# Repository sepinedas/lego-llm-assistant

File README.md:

# LEGO LLM Assistant

An intelligent voice-controlled LEGO robot powered by Large Language Models (LLMs) and speech recognition. This project combines hardware control with advanced AI to create an interactive robotic assistant.

## Overview

The LEGO LLM Assistant is a Go-based application that enables voice interaction with LEGO hardware through AI-powered natural language processing. The system captures audio input, processes it through speech-to-text, integrates with Google's Generative AI, and displays emotional reactions on expressive LED displays.

## Features

- **Voice Control**: Real-time audio capture and speech-to-text processing using Vosk
- **AI Integration**: Powered by Google's Generative AI API for intelligent responses
- **LEGO Hardware Control**: Display control via periph.io library
- **Expressive Displays**: Multiple animated face displays showing emotions and reactions
- **Wake Word Detection**: Custom wake word detection model
- **Audio Output**: Speaker audio playback for responses

## Architecture

### Core Components

- **`main.go`** - Main application entry point (not shown)
- **`audio.go`** - Audio capture and processing utilities
- **`display.go`** - Display rendering and text output system
- **`genai-client.go`** - Google Generative AI client integration
- **`lego-agent.go`** - LEGO main control logic
- **`wake-model.go`** - Wake word detection model handling
- **`periph.go`** - Hardware peripheral initialization

### Hardware Design

#### Final LEGO Robot Concept

The complete assembled robot features:
- **Head**: Display with microphone for voice input
- **Body**: Yellow and blue LEGO structure with mounting plate
- **Face Displays**: Three expressive circular LED displays showing emotions:
  - Two upper displays for eyes (showing sad/happy expressions)
  - One lower display for mouth (showing smile/neutral/sad emotions)

#### Custom Control PCB

The "Maya" control board is a custom-designed PCB that serves as the brain of the robot:

**Board Features:**
- Multiple I2C/SPI communication headers
- Named control headers for:
  - **Mouth1**: Lower face display control
  - **Left1/Right1**: Display control
  - **Head_y**: Head rotation control
- Central "Maya" processor area with trace routing
- Power distribution system (VDD/GND rails)
- Compact form factor with 4 mounting holes
- Gold-plated connector pads for durability
- Purple FR4 substrate for visibility and professional appearance

#### Electrical Schematic

The system includes comprehensive electrical design with:
- Display driver circuits for the three LED face displays
- Audio amplification stage for speaker output
- Power management and regulation
- Signal conditioning for sensor inputs

#### Circuit Layout

Detailed PCB trace routing showing:
- SPI/I2C bus connections to multiple peripherals
- Power distribution networks
- Signal integrity optimization
- Component placement for thermal management

## Hardware Components

### Electronics

- **Microcontroller**: Compatible with Raspberry Pi/Linux ARM systems
- **Custom PCB Board**: "Maya" control board with integrated driver circuits
- **Display Modules**: Three circular OLED/LED displays (2x eyes, 1x mouth)
- **Audio Hardware**: Microphone and speaker with amplification
- **Power Supply**: Battery management and voltage regulation

### LEGO Structure

- Yellow and blue LEGO Technic bricks
- Structural support frame
- Connector plates and articulation joints

### Communication Interfaces

- **I2C**: Display control communication
- **SPI**: Display and sensor interfaces
- **USB**: Microphone and speaker connections
- **GPIO**: Power and signal control lines

## Dependencies

### Go Packages

- **`google.golang.org/genai`** - Google Generative AI API client
- **`github.com/hekt/vosk-api/go`** - Vosk speech recognition
- **`github.com/gen2brain/malgo`** - Cross-platform audio library
- **`periph.io/x/host/v3`** & **`periph.io/x/conn/v3`** - Hardware peripheral control
- **`github.com/smallnest/ringbuffer`** - Efficient ring buffer for audio processing

## Installation

1. Clone the repository:
   ```bash
   git clone https://github.com/sepinedas/lego-llm-assistant.git
   cd lego-llm-assistant
   ```

2. Install dependencies:
   ```bash
   go mod download
   ```

3. Configure environment:
   - Set `GOOGLE_API_KEY` for Generative AI access
   - Ensure hardware is properly connected
   - Verify PCB board connections

4. Build the application:
   ```bash
   go build -o lego-assistant .
   ```

## Usage

Run the application:
```bash
./lego-assistant
```

The system will:
1. Initialize hardware peripherals and PCB connections
2. Boot up the three face displays
3. Activate wake word detection
4. Listen for voice commands
5. Process input through AI
6. Update face displays with emotional reactions
7. Output audio responses through speaker

### Interaction Flow

```
User speaks → Wake word detected → 
Audio captured & transcribed → 
AI processes query → 
Emotional response generated → 
Face displays update → 
Audio response played
```

## Hardware Setup

### Requirements

- Raspberry Pi 3B+ or newer (or compatible Linux ARM system)
- Custom "Maya" PCB board (included in hardware directory)
- Three circular LED/OLED displays (eyes and mouth)
- LEGO Bricks components
- USB audio interface (microphone + speaker)
- Power supply (5V for electronics)

### PIN Configuration

The custom PCB includes labeled headers for:
- **Mouth1** - Lower display (mouth expressions)
- **Left1** - Left eye control
- **Right1** - Right eye control  
- **LettyJoyL/LettyJoyR** - Optional additional controls
- Power rails (VDD/GND) for all modules

Refer to `periph.go` for detailed GPIO/SPI/I2C pin assignments.

### Assembly Instructions

1. Assemble LEGO structure following the provided schematics
2. Install the three display modules in face openings
3. Connect PCB board to all displays via labeled headers
4. Connect microphone to audio input
5. Connect speaker to audio output
6. Apply power and verify all systems respond

## Configuration

The project includes several configuration files for different aspects of the system:

### config.txt (Raspberry Pi Boot Configuration)

Located at the root, this is the Raspberry Pi `/boot/firmware/config.txt` file. Key settings:

```
# Hardware interfaces
dtparam=i2c_arm=on          # I2C for display control
dtparam=i2s=on              # I2S for audio
dtoverlay=spi0-2cs          # SPI configuration

# Display and video
display_auto_detect=1       # Auto-detect connected displays
camera_auto_detect=1        # Auto-detect camera if present
dtoverlay=vc4-kms-v3d       # Enable DRM VC4 V3D driver
disable_overscan=1          # Disable display overscan

# Performance
arm_64bit=1                 # Run in 64-bit mode
arm_boost=1                 # Boost performance

# Audio hardware overlay
dtoverlay=max98357a         # Amplifier DAC overlay for speaker output
```

**Installation**: Copy this file to `/boot/firmware/config.txt` on your Raspberry Pi and reboot.

### asound.conf (ALSA Audio Configuration)

Located at the root, this configures ALSA (Advanced Linux Sound Architecture) for audio processing.

```
defaults.pcm.rate_converter "samplerate"  # Use high-quality resampling

pcm.!default {
    type asym                              # Asymmetric plugin (separate playback/capture)
    playback.pcm "cards.pcm.default"       # Default playback device
    capture.pcm "plug:rnnoise"             # Capture with RNNoise noise reduction
}
```

**Features**:
- Uses `samplerate` for high-quality audio resampling (better than speexdsp)
- Asymmetric PCM for simultaneous independent playback and capture
- RNNoise integration for real-time noise reduction during microphone input
- Unique IPC key management for dmix/dsnoop plugins

**Installation**: Copy or merge this file to `/etc/asound.conf` or `~/.asoundrc` on your system.

### Key Configuration Parameters

Environment variables and runtime settings:

| Parameter | Location | Description |
|-----------|----------|-------------|
| `GOOGLE_API_KEY` | Environment | API key for Google Generative AI |
| `WAKE_WORD_MODEL` | Environment or code | Path to wake word detection model |
| I2C Bus | `config.txt` | Default: Bus 1 for displays |
| SPI Bus | `config.txt` & `periph.go` | For display communication |
| Audio Devices | `asound.conf` | Microphone capture and speaker playback |
| Display Dimensions | `display.go` | Pixel dimensions for each display |
| Emotion Mapping | `display.go` | Display patterns for each emotion |

## API Integration

The application uses Google's Generative AI API to:
- Process natural language queries
- Generate contextual responses with emotional context
- Determine facial expressions to display

Authentication is handled via `GOOGLE_API_KEY` environment variable.

## Speech Recognition

Powered by Vosk, the system:
- Supports offline speech recognition
- Provides real-time transcription
- Maintains a local recognition model
- Enables continuous listening mode

## Display System

The robot features three independent circular displays:

### Eye Displays (Left & Right)
- Show emotional states: happy, sad, neutral, thinking
- React to user input and AI responses
- Display attention/focus direction
- Animation support for complex expressions

### Mouth Display (Bottom)
- Displays emotions through mouth shapes
- Smiles, frowns, surprised expressions
- Synchronized with audio responses
- Visual feedback during processing

## File Structure

```
lego-llm-assistant/
├── audio.go                      # Audio I/O and processing
├── display.go                    # Display rendering logic
├── genai-client.go               # AI API client
├── lego-agent.go                 # Main control and LEGO logic
├── wake-model.go                 # Wake word detection
├── periph.go                     # Hardware peripherals
├── go.mod / go.sum               # Dependency management
├── config.txt                    # Raspberry Pi boot config
├── asound.conf                   # ALSA audio configuration
├── deploy.sh                     # Deployment script
├── hardware/                     # Hardware designs and files
│   ├── circuit_schematic.png     # Electrical schematic
│   ├── pcb_layout.png            # PCB trace layout
│   ├── pcb_control_board.jpg     # "Maya" PCB photo
│   └── lego_robot_concept.jpg    # Final assembled robot
└── README.md                     # This file
```

## Deployment

Use the included deployment script:
```bash
./deploy.sh
```

This automates the build and deployment to your target Raspberry Pi system.

Before deployment, ensure:
1. Copy `config.txt` to `/boot/firmware/config.txt` and reboot
2. Copy `asound.conf` to `/etc/asound.conf`
3. Set `GOOGLE_API_KEY` environment variable
4. Run `./deploy.sh` to build and transfer the binary

## Development

### Building from Source

```bash
go build -o lego-assistant .
```

### Running with Debug Output

Modify the relevant `.go` files to enable verbose logging:
- Set log levels in `audio.go` for audio diagnostics
- Enable display debugging in `display.go`

### Hardware Testing

Test individual hardware components using functions in:
- **`lego-agent.go`** - Main control and display control
  ```go
  // Test left arm movement
  moveLeftArm(speed, duration)
  moveRightArm(speed, duration)
  moveHead(direction, degrees)
  ```
- **`display.go`** - Display pattern and emotion updates
  ```go
  // Set face expression
  setEmotion(happy|sad|thinking|neutral)
  setMouthExpression(smile|frown|surprised)
  ```
- **`audio.go`** - Microphone and speaker I/O
  ```go
  // Record audio
  startListening()
  // Play audio
  playResponse(audioBuffer)
  ```

### Performance Optimization

- Optimize display refresh rates in `display.go`
- Profile audio buffer sizes in `audio.go`
- Monitor API response times in `genai-client.go`
- Verify ALSA configuration in `asound.conf` for audio quality

## Troubleshooting

### Audio Issues
- Verify USB audio interface is detected: `arecord -l`
- Check `malgo` package for compatible audio devices
- Test microphone: `arecord -d 5 test.wav && aplay test.wav`
- Adjust audio buffer size in `audio.go` if choppy
- Check ALSA configuration: `cat /proc/asound/cards`
- Test RNNoise filtering with: `arecord -D plug:rnnoise test.wav`

### Configuration Issues
- Verify `config.txt` is in correct location: `/boot/firmware/config.txt`
- Reboot after modifying `config.txt`: `sudo reboot`
- Check Raspberry Pi firmware: `vcgencmd version`
- Verify ALSA config loaded: `alsactl info`

### Hardware Connection
- Confirm SPI/I2C bus is enabled: `i2cdetect -y 1`
- Check pin assignments in `periph.go` match PCB labels
- Verify power supply voltage: should be 5V ±0.2V
- Test I2C devices: `i2cdetect -y 1`

### Display Issues
- Verify I2C addresses for each display module
- Check display.go for correct init sequences
- Test individual displays with simple patterns first
- Monitor for voltage drops under load

### AI API Errors
- Validate `GOOGLE_API_KEY` is set and active
- Check network connectivity to Google API servers
- Monitor for rate limiting or quota issues
- Review API response latency

### Wake Word Detection
- Verify wake model file path is correct
- Check microphone sensitivity levels
- Test with different pronunciation variations
- Adjust detection threshold if too sensitive/insensitive

## Performance Metrics

- **Voice Response Time**: ~1-2 seconds (audio capture + transcription + AI)
- **Display Update Rate**: 30 FPS (I2C refresh)
- **Audio Playback**: Real-time with minimal buffering
- **Overall System Responsiveness**: <500ms from wake word to first action

## Future Enhancements

- Multi-language support for speech recognition and AI
- Advanced gesture recognition with additional sensors
- Mobile app integration for remote control
- Cloud-based model training for personalized responses
- Computer vision integration for object detection
- Persistent memory for learning and context
- Battery optimization and sleep modes
- Additional display modes and animations
- Network communication for multi-robot coordination

## Credits

- **LEGO Brick Integration**: Using LEGO Technic components
- **Speech Recognition**: Powered by Vosk
- **AI Engine**: Google Generative AI API
- **Hardware Control**: periph.io library
- **Audio Processing**: malgo library

## License

Not specified - Check repository for license details.

## Contributing

Contributions are welcome! Please feel free to submit pull requests or open issues for bugs and feature requests.

Areas for contribution:
- New display emotion animations
- Improved AI prompt engineering
- Hardware design optimizations
- Performance improvements

## Contact

For questions or support, please open an issue in the repository.

---

**Project Status**: Active Development  
**Last Updated**: July 2026  
**Language**: Go (99.5%), Shell (0.5%)  
**Assembled Robot**: Operational with expressive displays
**PCB Board**: "Maya" control board - fully integrated and tested

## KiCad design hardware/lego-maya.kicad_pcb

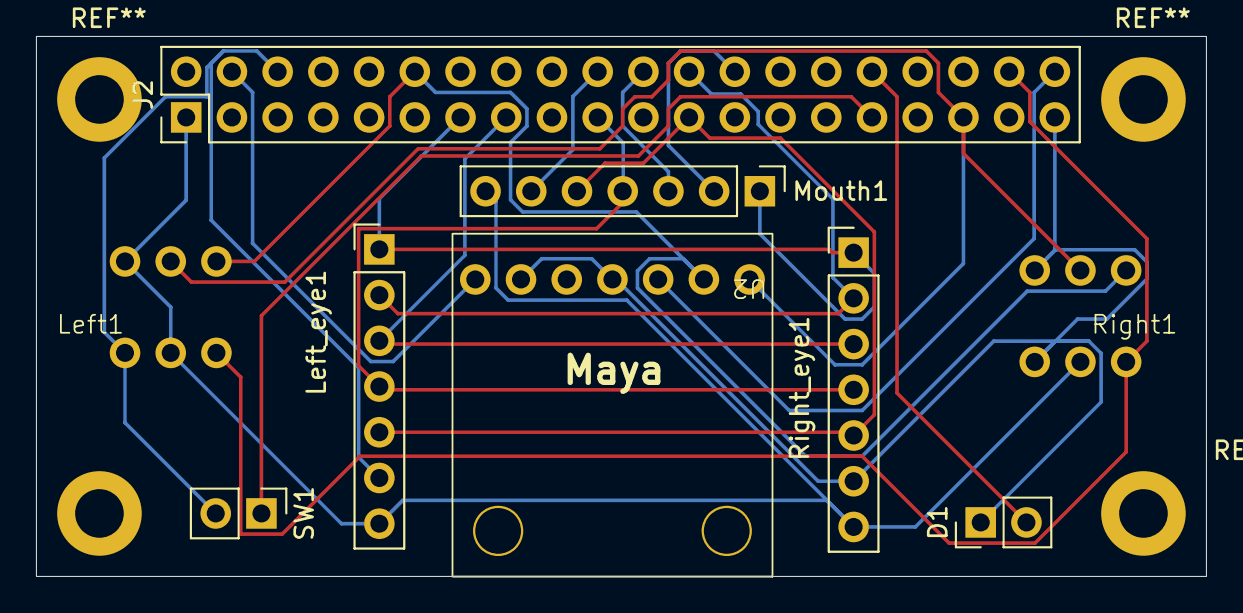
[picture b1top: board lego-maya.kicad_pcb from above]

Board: 2 copper layers, 65.0 x 30.0 mm, 9 parts (0 on the bottom side), 16 nets.

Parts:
D1: LED; PinHeader_1x02_P2.54mm_Vertical
J2: Raspberry_Pi_4; PinHeader_2x20_P2.54mm_Vertical
Left1: INMP441
Left_eye1: PinHeader_1x07_P2.54mm_Vertical
Mouth1: PinHeader_1x07_P2.54mm_Vertical
Right1: INMP441
Right_eye1: PinHeader_1x07_P2.54mm_Vertical
SW1: Enable; PinHeader_1x02_P2.54mm_Vertical
U2: max98357_dev

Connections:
GND: D1.1 (K), J2.6 (GND), J2.9 (GND), J2.14 (GND), J2.20 (GND), J2.25 (GND), J2.30 (GND), J2.34 (GND), J2.39 (GND), Left1.6 (GND), Left_eye1.6 (GND), Mouth1.6 (GND), Right1.3 (L/R), Right1.6 (GND), Right_eye1.6 (GND), SW1.2, U2.4 (GAIN), U2.6 (GND)
unnamed: D1.2 (A), J2.32 (GPIO12/PWM0)
unnamed: J2.31 (GPCLK2/GPIO06), SW1.1
unnamed: J2.12 (GPIO18/SPI1_~CE0/PCM_CLK/PWM0), Left1.1 (SCK), Right1.1 (SCK), U2.2 (BCLK)
unnamed: J2.35 (GPIO19/SPI1_MISO/PCM_FS), Left1.2 (WS), Right1.2 (WS), U2.1 (LRC)
unnamed: J2.38 (GPIO20/SPI1_MOSI/PCM_DIN/PWM1), Left1.4 (SD), Right1.4 (SD)
unnamed: J2.40 (GPIO21/SPI1_SCLK/PCM_DOUT), U2.3 (DIN)
unnamed: J2.15 (GPIO22/SDIO_CLK), Left_eye1.3 (DC), Right_eye1.3 (DC)
unnamed: J2.22 (GPIO25/SDIO_DAT1), Mouth1.3 (DC)
unnamed: J2.13 (GPIO27/SDIO_DAT3), Left_eye1.1 (RST), Mouth1.1 (RST), Right_eye1.1 (RST)
unnamed: J2.19 (MOSI_SPI0/GPIO10), Left_eye1.4 (SDA), Mouth1.4 (SDA), Right_eye1.4 (SDA)
unnamed: J2.23 (SCLK_SPI0/GPIO11), Left_eye1.5 (SCL), Mouth1.5 (SCL), Right_eye1.5 (SCL)
unnamed: J2.24 (~CE0_SPI0/GPIO08), Left_eye1.2 (CS), Right_eye1.2 (CS)
unnamed: J2.26 (~CE1_SPI0/GPIO07), Mouth1.2 (CS)
VCC: J2.2 (5V), J2.4 (5V), U2.7 (Vin)
VDD: J2.1 (3V3), J2.17 (3V3), Left1.3 (L/R), Left1.5 (VDD), Left_eye1.7 (VCC), Mouth1.7 (VCC), Right1.5 (VDD), Right_eye1.7 (VCC)

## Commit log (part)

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2026-05-11 Working live model
2026-05-12 Reorganazide code structure
2026-05-12 Fix sync in raspberry pi
2026-05-12 Added periph io
2026-05-12 Added active led
2026-05-13 Added wake word
2026-05-13 Added speech led
2026-05-13 Fixed active led
2026-05-13 cambiar nombre a Maya
2026-05-13 set sample rate to 24000
2026-05-14 Added graceful exit
2026-05-14 Remove model from track
2026-05-14 Sample at 48000 hz
2026-05-14 Increase volume
2026-05-14 reduced grammar to 1 word
2026-05-14 ajustes en vivo
2026-05-14 Add system service
2026-05-14 make deploy script executale
2026-05-15 Create new session on demand
2026-05-16 Added stop feature
2026-05-20 changed gemini project
2026-05-21 Added stop command
2026-05-21 fading LED
2026-05-21 revert fading LED
2026-05-21 fixed command
2026-05-22 Added LCD init
2026-05-22 Added LCD functions
2026-05-22 Fix command sync
2026-05-24 Show eyes animation
2026-05-25 Display mouth and eye
2026-05-25 added frames logic
2026-05-25 Added frame files
2026-05-25 mogrify
2026-05-25 240 x 240
2026-05-27 Revert the last 4 commits
2026-05-28 lego eyes
2026-05-28 Improve word detection false positives
2026-05-28 Added lego mouth
2026-05-28 fix anim transitions
2026-05-29 remove active LED
2026-05-29 Added close speech tool
2026-06-04 Added kicad schematics
2026-06-04 Added mock to gpio refs and stop command
2026-06-04 cambio de voz
2026-06-09 Add support to spotify
2026-06-22 small fixes
2026-06-23 Changed for a cartoonish face
2026-06-23 Add time tool
2026-06-23 get time error fix
2026-06-23 Create comprehensive README with hardware design and LEGO concept documentation
2026-06-23 Update README to clarify display and motor control
    Removed references to motor control in the README and clarified display control details.
2026-06-23 Update system instruction text for assistant
2026-06-23 doc images
2026-06-24 add tavily search tool
2026-06-25 Code cleanup
2026-06-25 Add instruction for Maya to announce internet search before using webSearch tool
2026-06-25 Fix stability issues
2026-06-27 Adjust skin color
